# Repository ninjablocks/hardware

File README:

These are the Designs for the **Ninja Block Cape** and **Sensor PCBs**. 
The files were created in the free/low cost EagleCad software available form [here](http://www.cadsoftusa.com/downloads/). 

Back Ninja Blocks on Kickstarter: [http://kck.st/y49ssb](http://kck.st/y49ssb)  or [Follow us on Twitter](http://twitter.com/ninjablocks).

As always if you have any questions or queries whatsoever, please don't hesitate to contact us on ninjas@ninjablocks.com .

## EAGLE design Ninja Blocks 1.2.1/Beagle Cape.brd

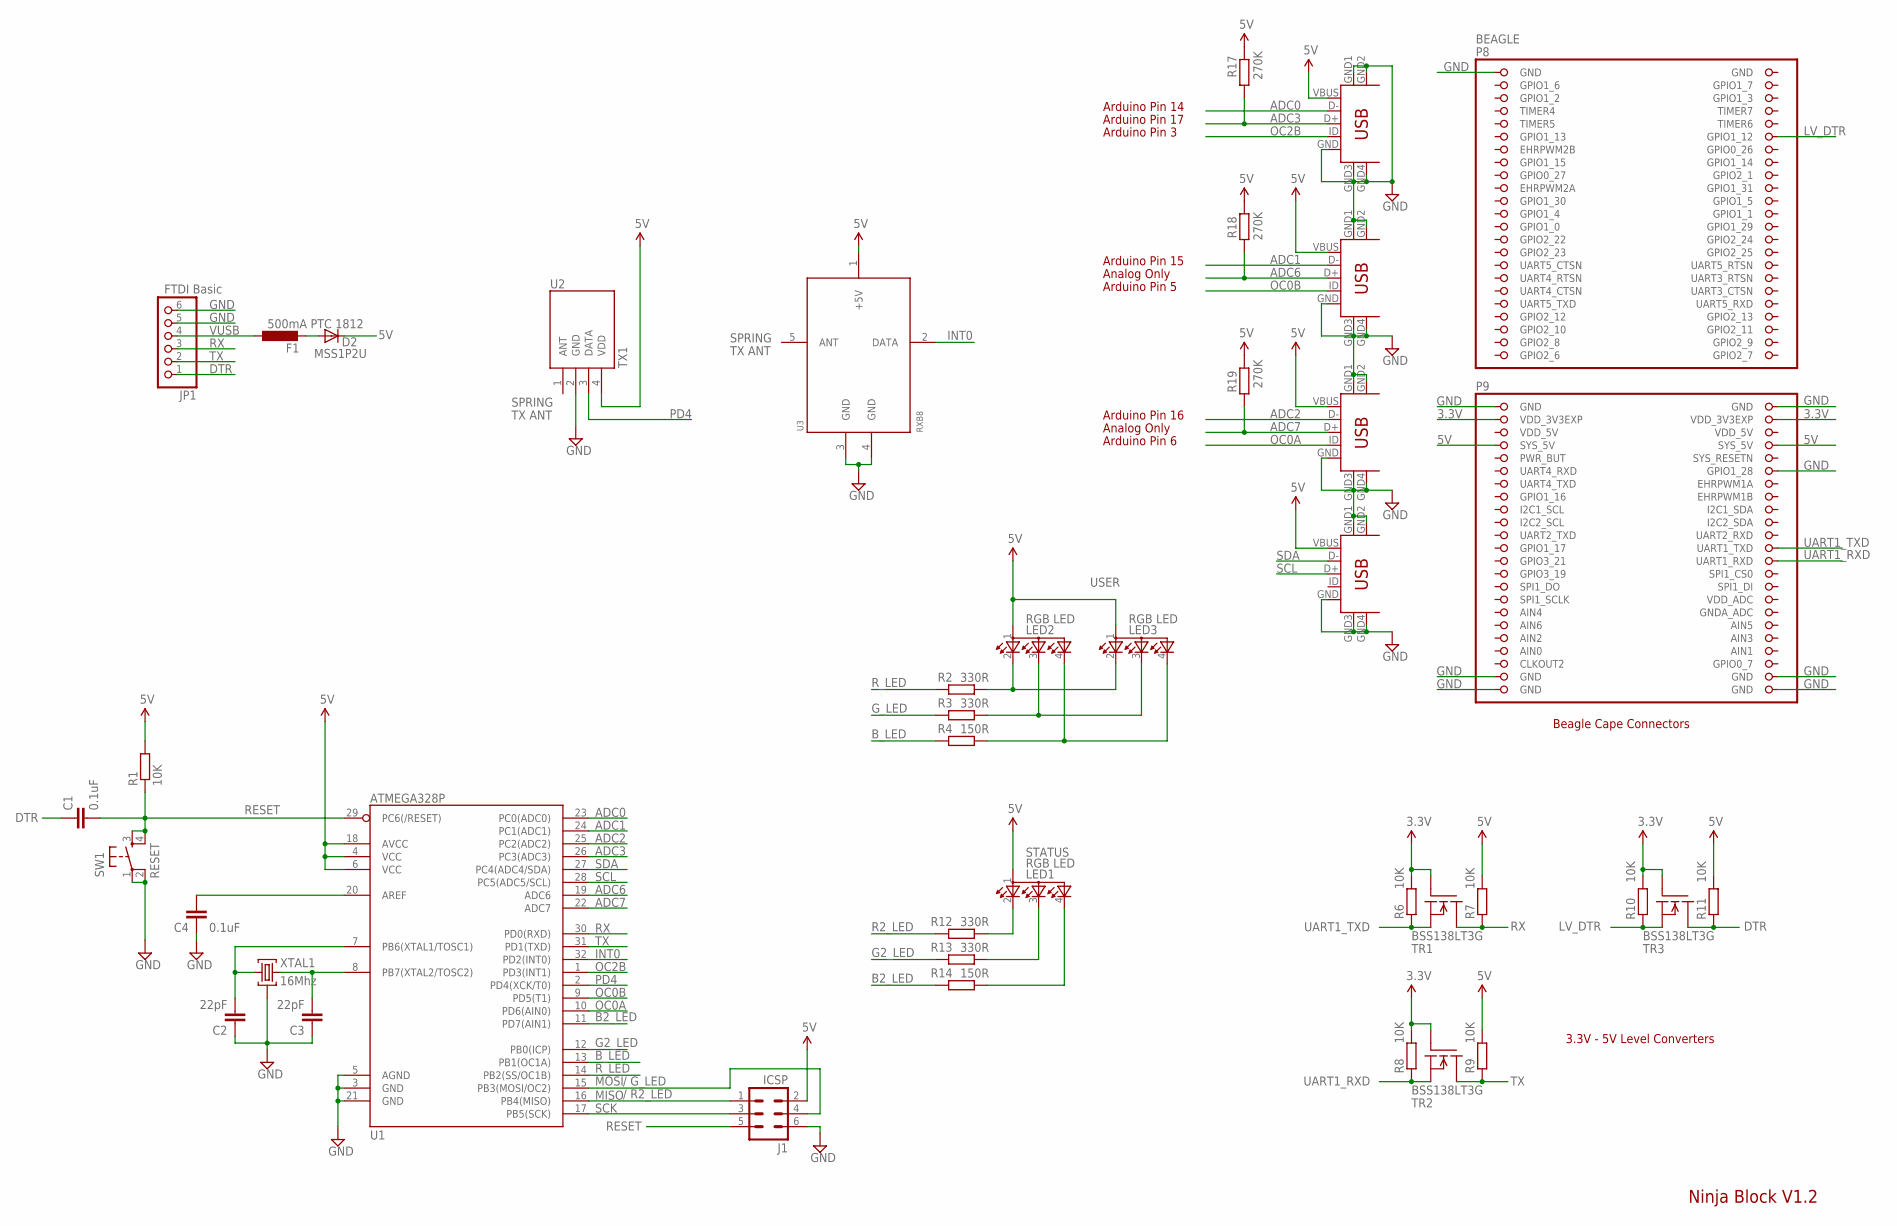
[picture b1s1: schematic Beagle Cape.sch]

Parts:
BEAGLE: BEAGLEBONE_OUTLINE; BEAGLEBONE_SHIELD
C1, C4: 0.1uF; C0603
C2, C3: 22pF; C0603
CON1, CON2, CON3: USB-MINIB; MOLEX_MINIUSB_B
D2: MSS1P2U; MICROSMP
F1: 500mA PTC 1812; L1812
I2C: USB-MINIB; MOLEX_MINIUSB_B
J1: ICSP; MA03-2
JP1: FTDI Basic; 1X06
LED1, LED2, LED3: RGB LED; AVAGO_LED
R1, R6, R7, R8, R9, R10, R11: 10K; R0603
R2, R3, R12, R13: 330R; R0603
R4, R14: 150R; R0603
R17, R18, R19: 270K; R0603
SW1: RESET; ALPS_SMD_TAC_SWITCH
TR1, TR2, TR3: BSS138LT3G; SOT23
U1: ATMEGA328P; TQFP32-08
U2: TX1
U3: RXB8
XTAL1: 16Mhz; HC49US-G

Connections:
3.3V: BEAGLE.49 (VDD_3V3EXP), BEAGLE.50 (VDD_3V3EXP), R6.1, R8.1, R10.1, TR1.1 (G), TR2.1 (G), TR3.1 (G)
5V: BEAGLE.53 (SYS_5V), BEAGLE.54 (SYS_5V), CON1.VBUS, CON2.VBUS, CON3.VBUS, D2.C, I2C.VBUS, J1.2, LED1.1 (A1), LED2.1 (A1), LED3.1 (A1), R1.2, R7.1, R9.1, R11.1, R17.1, R18.1, R19.1, U1.4 (VCC), U1.6 (VCC), U1.18 (AVCC), U2.4 (VDD), U3.1 (+5V)
ADC0: CON1.D-, U1.23 (PC0(ADC0))
ADC1: CON2.D-, U1.24 (PC1(ADC1))
ADC2: CON3.D-, U1.25 (PC2(ADC2))
ADC3: CON1.D+, R17.2, U1.26 (PC3(ADC3))
ADC6: CON2.D+, R18.2, U1.19 (ADC6)
ADC7: CON3.D+, R19.2, U1.22 (ADC7)
AIN0: BEAGLE.85 (AIN0)
AIN3: BEAGLE.84 (AIN3)
B2_LED: R14.2, U1.11 (PD7(AIN1))
B_LED: R4.2, U1.13 (PB1(OC1A))
DTR: C1.1, JP1.1, R11.2, TR3.3 (D)
G2_LED: R13.2, U1.12 (PB0(ICP))
GND: BEAGLE.1 (GND), BEAGLE.2 (GND), BEAGLE.47 (GND), BEAGLE.48 (GND), BEAGLE.58 (GPIO1_28), BEAGLE.89 (GND), BEAGLE.90 (GND), BEAGLE.91 (GND), BEAGLE.92 (GND), C2.1, C3.1, C4.1, CON1.GND, CON1.GND1 (MTN1), CON1.GND2 (MTN2), CON1.GND3 (MTN3), CON1.GND4 (MTN4), CON2.GND, CON2.GND1 (MTN1), CON2.GND2 (MTN2), CON2.GND3 (MTN3), CON2.GND4 (MTN4), CON3.GND, CON3.GND1 (MTN1), CON3.GND2 (MTN2), CON3.GND3 (MTN3), CON3.GND4 (MTN4), I2C.GND, I2C.GND1 (MTN1), I2C.GND2 (MTN2), I2C.GND3 (MTN3), I2C.GND4 (MTN4), J1.6, JP1.5, JP1.6, SW1.1, SW1.2, U1.3 (GND), U1.5 (AGND), U1.21 (GND), U2.2 (GND), U3.3 (GND), U3.4 (GND), XTAL1.GND (2)
GPIO1_6: BEAGLE.3 (GPIO1_6)
GPIO1_7: BEAGLE.4 (GPIO1_7)
GPIO2_6: BEAGLE.45 (GPIO2_6)
GPIO2_7: BEAGLE.46 (GPIO2_7)
GPIO2_8: BEAGLE.43 (GPIO2_8)
GPIO2_9: BEAGLE.44 (GPIO2_9)
GPIO2_11: BEAGLE.42 (GPIO2_11)
INT0: U1.32 (PD2(INT0)), U3.2 (DATA)
LV_DTR: BEAGLE.12 (GPIO1_12), R10.2, TR3.2 (S)
MISO: J1.1, R12.2, U1.16 (PB4(MISO))
MOSI: J1.4, R3.2, U1.15 (PB3(MOSI/OC2))
unnamed: C2.2, U1.7 (PB6(XTAL1/TOSC1)), XTAL1.1
unnamed: LED2.2 (R2), LED3.2 (R2), R2.1
unnamed: C3.2, U1.8 (PB7(XTAL2/TOSC2)), XTAL1.2 (3)
unnamed: C4.2, U1.20 (AREF)
unnamed: LED2.3 (G3), LED3.3 (G3), R3.1
unnamed: LED2.4 (B4), LED3.4 (B4), R4.1
unnamed: LED1.2 (R2), R12.1
unnamed: LED1.3 (G3), R13.1
unnamed: LED1.4 (B4), R14.1
unnamed: D2.A, F1.2
OC0A: CON3.ID, U1.10 (PD6(AIN0))
OC0B: CON2.ID, U1.9 (PD5(T1))
OC2B: CON1.ID, U1.1 (PD3(INT1))
PD4: U1.2 (PD4(XCK/T0)), U2.3 (DATA)
RESET: C1.2, J1.5, R1.1, SW1.3, SW1.4, U1.29 (PC6(/RESET))
RX: JP1.3, R7.2, TR1.3 (D), U1.30 (PD0(RXD))
R_LED: R2.2, U1.14 (PB2(SS/OC1B))
SCK: J1.3, U1.17 (PB5(SCK))
SCL: I2C.D+, U1.28 (PC5(ADC5/SCL))
SDA: I2C.D-, U1.27 (PC4(ADC4/SDA))
TX: JP1.2, R9.2, TR2.3 (D), U1.31 (PD1(TXD))
UART1_RXD: BEAGLE.72 (UART1_RXD), R8.2, TR2.2 (S)
UART1_TXD: BEAGLE.70 (UART1_TXD), R6.2, TR1.2 (S)
VDD_5V: BEAGLE.51 (VDD_5V), BEAGLE.52 (VDD_5V)
VUSB: F1.1, JP1.4

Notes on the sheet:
Ninja Block V1.2
3.3V - 5V Level Converters
Beagle Cape Connectors
Arduino Pin 14
Arduino Pin 17
Arduino Pin 3
Arduino Pin 15
Analog Only
Arduino Pin 5
Arduino Pin 16
Arduino Pin 6
G_LED
/ G_LED
STATUS
USER
/ R2_LED
R2_LED
SPRING
TX ANT

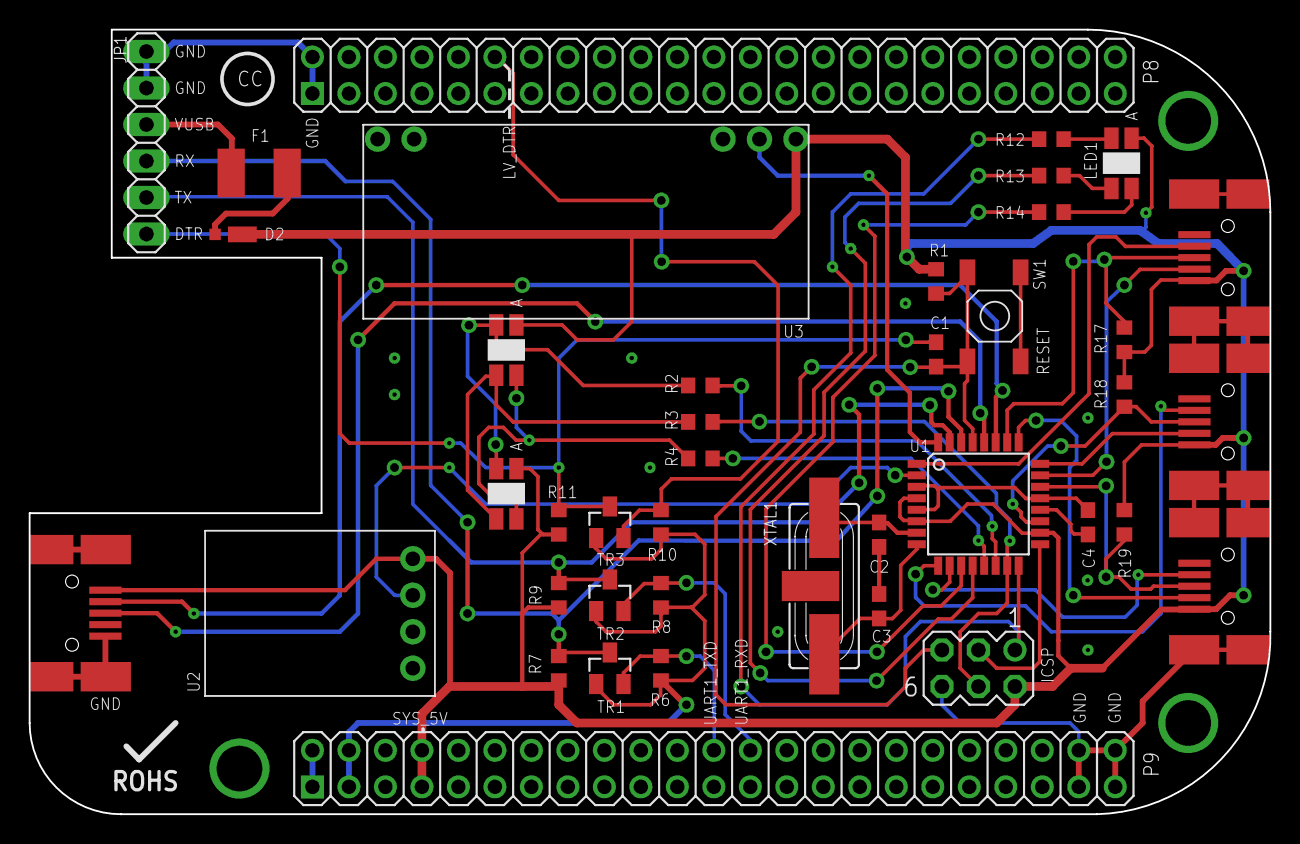
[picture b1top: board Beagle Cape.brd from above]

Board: 2 copper layers, 86.4 x 54.6 mm, 40 parts (0 on the bottom side), 42 nets.

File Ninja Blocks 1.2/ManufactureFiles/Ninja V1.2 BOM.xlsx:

Ninja Block V1.2 BOM 24th August 2012
Part | Value | Package | Manufacturer | Part Number | Source
P8, P9 | 2x23 pin header
C1,C4 | 0.1uF | C0603 | MULTICOMP | MCCA000255 | http://au.element14.com/multicomp/mcca000255/mlcc-0603-x7r-5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
C2,C3 | 22pF | C0603 | MULTICOMP | MCCA000196 | http://au.element14.com/multicomp/mcca000196/mlcc-0603-np0-5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
CON1, 2, 3 | USB-MINIB | MOLEX_MINIUSB_B | MOLEX | 67503-1030 | http://au.element14.com/molex/67503-1030/mini-usb-type-b-rec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
D2 | MSS1P2U | MICROSMP | VISHAY | MSS1P2U-M3/89A | http://www.newark.com/vishay-general-semiconductor/mss1p2u-m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
F1 | 500mA PTC 1812 | L1812 | LITTELFUSE | 1812L050PR | http://www.digikey.com/product-detail/en/1812L050PR/F2150CT-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
I2C | USB-MINIB | MOLEX_MINIUSB_B | Not Installed | Not Installed | Not Installed
J1 | ICSP | MA03-2 | Not Installed | Not Installed | Not Installed
JP1 | FTDI Basic | 1X06 | Not Installed | Not Installed | Not Installed
LED1, LED2, LED3 | AVAGO_RGB_LED | AVAGO_LED | AVAGO | HSMF-C118 | http://www.digikey.com/scripts/dksearch/dksus.dll?vendor=0&k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
R2,R3,R12,R13 | 330R | R0603 | MULTICOMP | MC 0.063W 0603 1% 330R | http://au.element14.com/multicomp/mc-0-063w-0603-1-330r/resi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
R4,R14 | 150R | R0603 | MULTICOMP | MC 0.063W 0603 1% 150R | http://au.element14.com/multicomp/mc-0-063w-0603-1-150r/resi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
R1,R6, R7,R8,R9,R10,R11 | 10K | R0603 | YAGEO | RC0603JR-0710KL | http://au.element14.com/yageo-phycomp/rc0603jr-0710kl/resist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
R17, R18, R19 | 270K | R0603 | YAGEO | RC0603FR-07270KL | http://au.element14.com/yageo-phycomp/rc0603fr-07270kl/resis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
RX_ANT, TX_ANT | Spring Antenna | PAD-01 | RELYRF | SPRING ANTENNA | RelyRF.com, 2.5cm long spring antenna
SW1 | RESET | ALPS_SMD_TAC_SWITCH | ALPS | SKQGADE010 | http://au.element14.com/alps/skqgade010/switch-tactile-smd-2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
TR1, TR2, TR3 | BSS138LT3G | SOT23 | ON SEMICONDUCTOR | BSS138LT3G | http://au.element14.com/on-semiconductor/bss138lt3g/n-channe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
U1 | ATMEGA328P | TQFP32-08 | ATMEL | ATMEGA328P-AU | http://www.digikey.com/product-detail/en/ATMEGA328P-AU/ATMEG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
U2 | TX1 | TX1 | RELYRF | TX1 | http://www.relyrf.com/rf/ask_transmitter/RY-TX1.htm
U3 | RXB8 | RXB8 | RELFRF | RXB8 | http://www.relyrf.com/rf/ask_receiver/RY-RXB8.htm
XTAL1 | 16Mhz | HC49US-G | ABRACON | ABLSG-16.384MHZ-D-2-Y-T | http://www.digikey.com/product-detail/en/ABLSG-16.384MHZ-D-2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

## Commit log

2012-02-17 First commit of hardware designs on the ninja blocks github account
2012-02-17 .DS_Store banished\!
2012-02-17 no more DS_Store
2012-02-28 Added some background info to the Readme.
2012-02-28 Changed from astrix to underscore for boldness
2012-02-28 changed the readme type to markdown
2012-05-30 added Ninja Breakout Board
2012-07-24 Complete Ninja Blocks hardware files
2012-08-17 Beagle Cape V1.2 Beta with built-in 433TX and RX.
2013-05-30 added files for manufacture
2013-05-30 copied v1.2 for v1.2.1
2013-05-30 Declare used pins of BB/BBB headers P8 and P9
2013-05-30 declaring difference from previous
2013-05-30 adding cam job file
2013-05-30 Move reset pin (P8,12). Ground GPIO1_28 pin (P9,12)
2013-05-30 generated gerber files
2013-05-31 adding image/text layers to top silkscreen overlay
2013-05-31 updated board revision to V1.2.1
2013-05-31 removed date from directory
2013-06-24 Top silkscreen masks 200, 201 (not 201, 202)
2013-06-24 Added RF Cape
2013-06-24 added RPI Crust
2013-06-24 Added component name layer to top silkscreen overlay
2013-06-27 Header Verification Spreadsheet
2013-07-01 further verifications
2013-07-02 GPIO2, 3 mislabled on P6
2013-07-03 Tested GPIO27 (labelled GPIO21 from RPi Model A)
2013-08-16 Added Case .STL files
